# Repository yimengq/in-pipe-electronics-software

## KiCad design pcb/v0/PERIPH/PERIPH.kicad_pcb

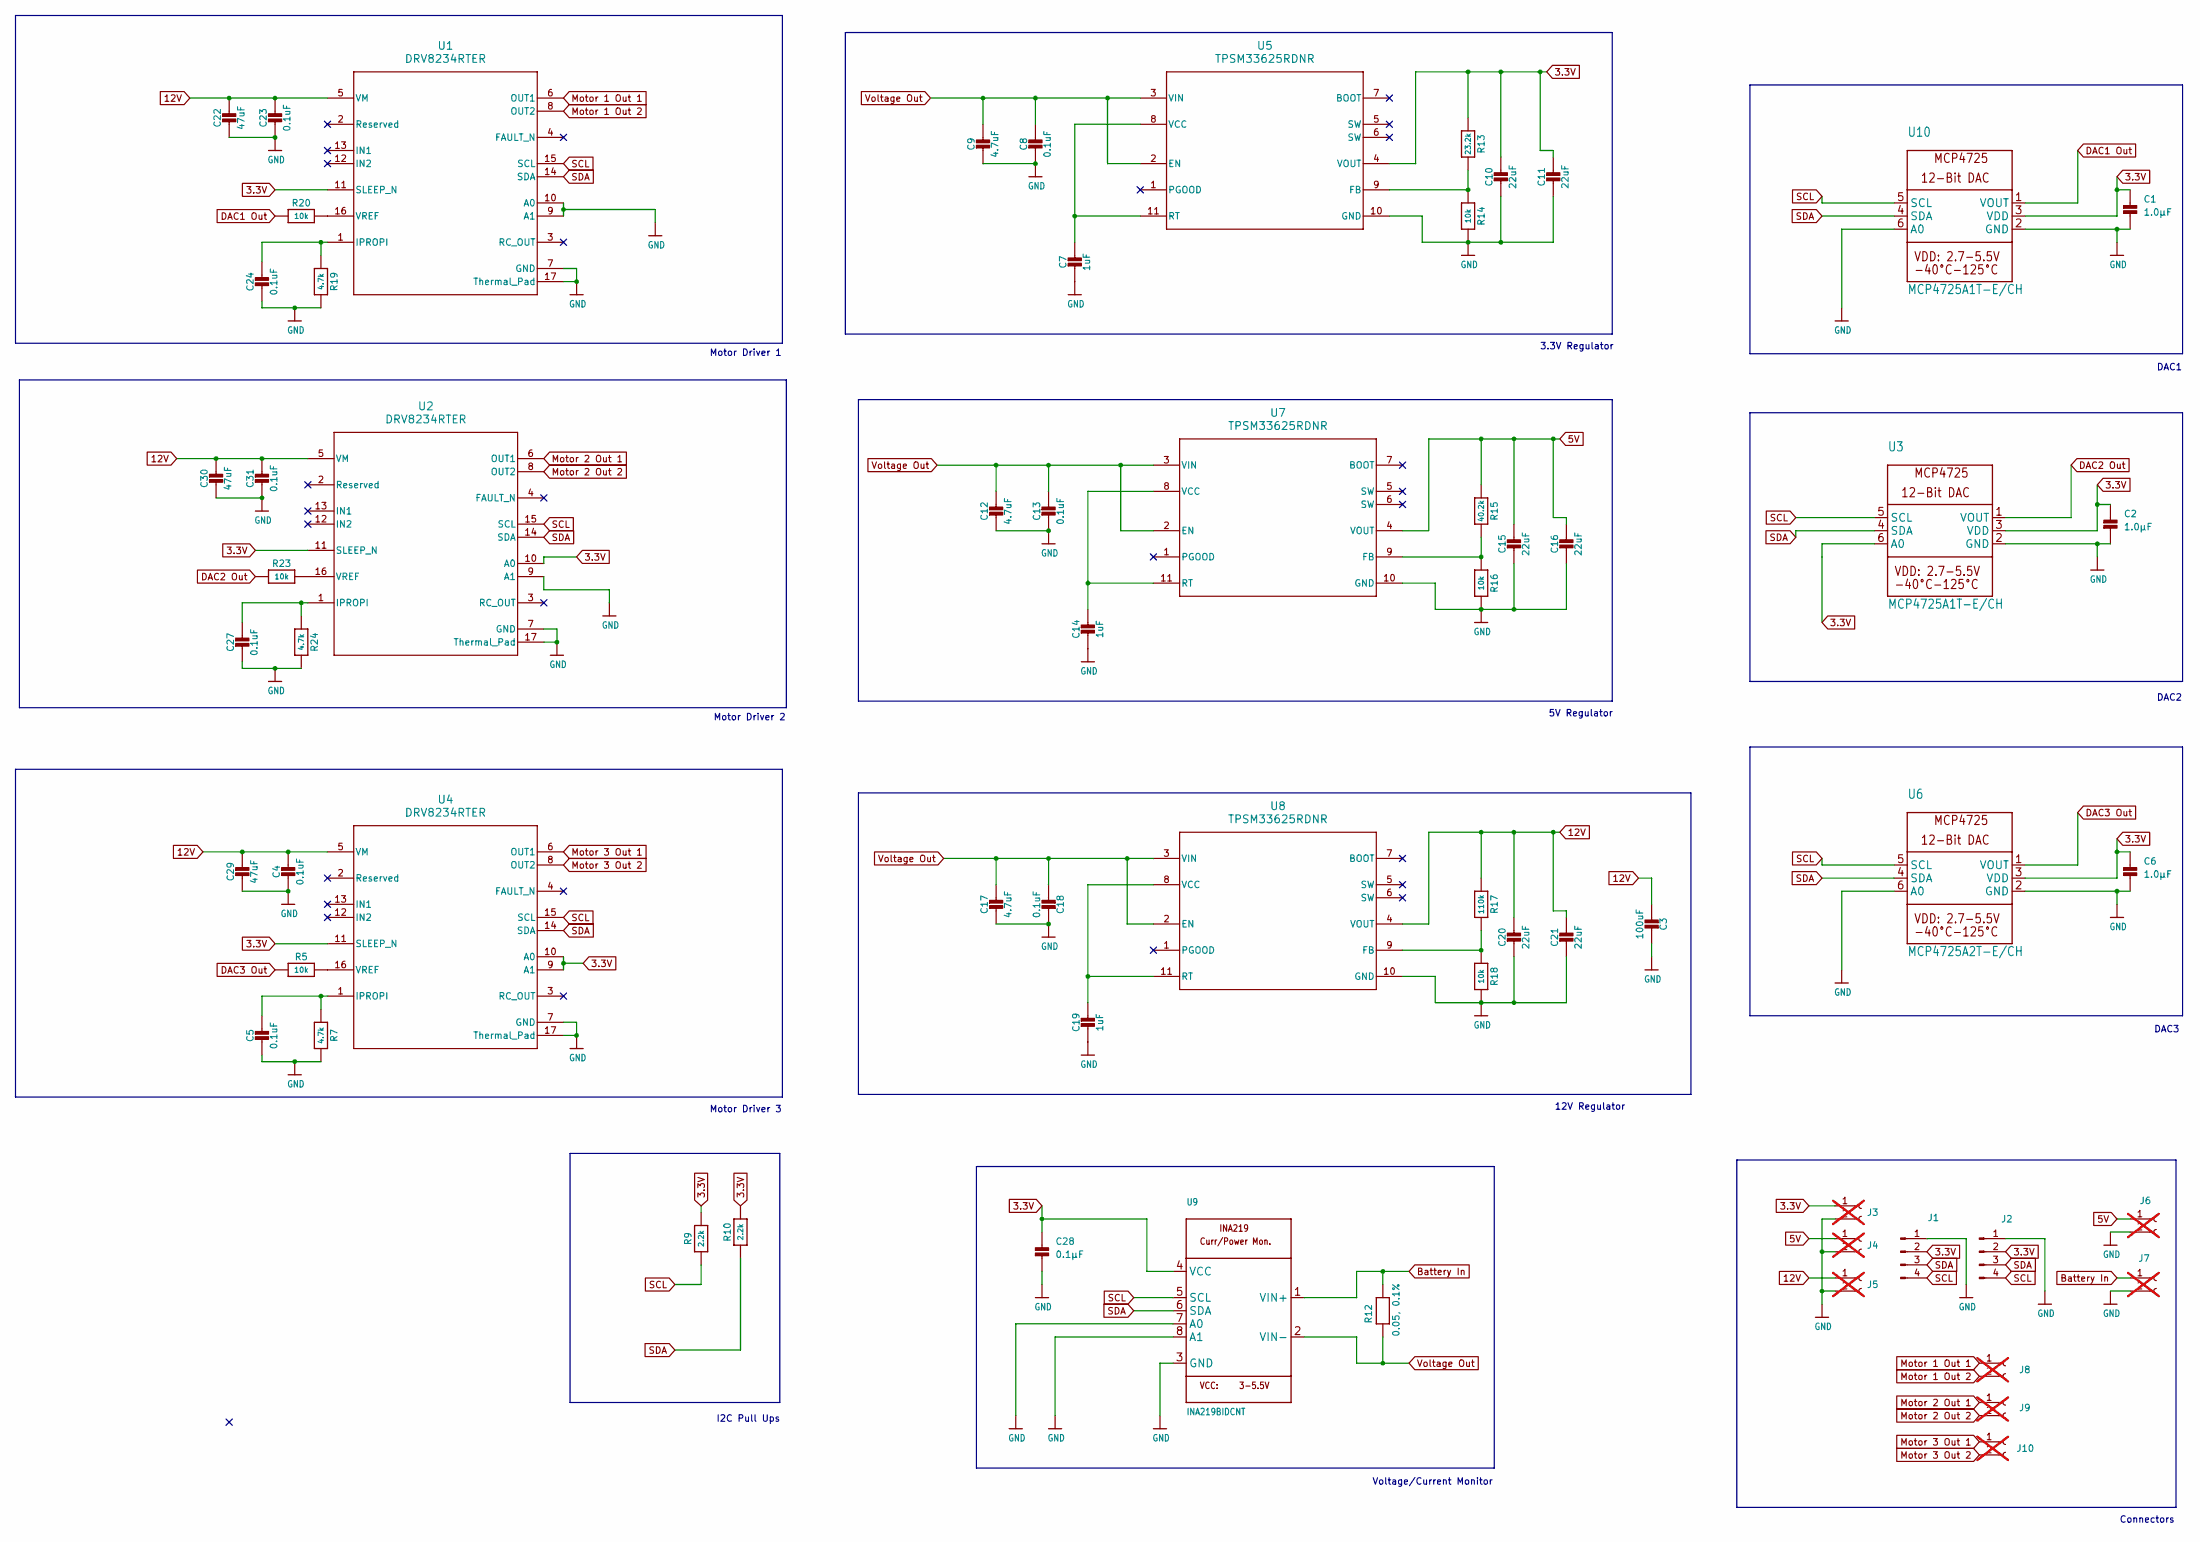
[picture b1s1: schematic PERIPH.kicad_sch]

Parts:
C1, C2, C6: 1.0µF; R_0603_1608Metric; MPN CL10B105KP8NNNC
C3: 100uF; PCAP_EEHZ_G_PAN-L; MPN EEH-ZA1H101P
C4, C5, C8, C13, C18, C23, C24, C27, C31: 0.1uF; R_0603_1608Metric; MPN C0603C104K3RACTU
C7, C14, C19: 1uF; R_0603_1608Metric; MPN CL10B105KP8NNNC
C9, C12, C17: 4.7uF; R_0805_2012Metric; MPN TMK212AB7475KG-T
C10, C11, C15, C16, C20, C21: 22uF; CAPC3225X270N; MPN CL32B226KAJNNNE
C22, C29, C30: 47uF; R_0603_1608Metric; MPN KTS250B476M76N0T00
C28: 0.1µF; R_0603_1608Metric; MPN C0603C104K3RACTU
J1, J2: JST SH 4 pin; CONN_SM04B-SRSS-TB_JST; MPN SM04B-SRSS-TB
J3, J4, J5, J6, J7, J8, J9, J10: Conn_01x02_Socket; PinSocket_1x02_P2.00mm_Vertical; not fitted
R5, R14, R16, R18, R20, R23: 10k; R_0603_1608Metric; MPN RC0603FR-0710KL
R7, R19, R24: 4.7k; R_0603_1608Metric; MPN CR0603-JW-472ELF
R9, R10: 2.2k; R_0603_1608Metric; MPN CR0603-FX-2201ELF
R12: 0.05, 0.1%; R_2512_6332Metric; MPN HoCG25122R050A4
R13: 23.2k; R_0603_1608Metric; MPN RC0603FR-0723K2L
R15: 40.2k; R_0603_1608Metric; MPN RC0603FR-0740K2L
R17: 110k; R_0603_1608Metric; MPN CRCW0603110KFKEAC
U1, U2, U4: DRV8234RTER; RTE0016C-IPC_A; MPN DRV8234RTER
U3, U10: MCP4725A1T-E/CH; SOT-23-6_MC_MCH; MPN MCP4725A1T-E/CH
U5, U7, U8: TPSM33625RDNR; RDN0011A-MFG; MPN TPSM33625RDNR
U6: MCP4725A2T-E/CH; SOT-23-6_MC_MCH; MPN MCP4725A2T-E/CH
U9: INA219BIDCNT; SOT65P280X145-8N; MPN INA219BIDCNT

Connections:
3.3V: C1.1, C2.1, C6.1, C10.1, C11.1, C28.1, J1.2, J2.2, J3.1, R9.2, R10.2, R13.1, U1.11 (SLEEP_N), U2.10 (A0), U2.11 (SLEEP_N), U3.3 (VDD), U3.6 (A0), U4.9 (A1), U4.10 (A0), U4.11 (SLEEP_N), U5.4 (VOUT), U6.3 (VDD), U9.4 (VCC), U10.3 (VDD)
5V: C15.1, C16.1, J4.1, J6.1, R15.1, U7.4 (VOUT)
12V: C3.1, C4.1, C20.1, C21.1, C22.1, C23.1, C29.1, C30.1, C31.1, J5.1, R17.1, U1.5 (VM), U2.5 (VM), U4.5 (VM), U8.4 (VOUT)
Battery In: J7.1, R12.2, U9.1 (VIN+)
DAC1 Out: R20.1, U10.1 (VOUT)
DAC2 Out: R23.1, U3.1 (VOUT)
DAC3 Out: R5.1, U6.1 (VOUT)
GND: C1.2, C2.2, C3.2, C4.2, C5.2, C6.2, C7.2, C8.2, C9.2, C10.2, C11.2, C12.2, C13.2, C14.2, C15.2, C16.2, C17.2, C18.2, C19.2, C20.2, C21.2, C22.2, C23.2, C24.2, C27.2, C28.2, C29.2, C30.2, C31.2, J1.1, J2.1, J3.2, J4.2, J5.2, J6.2, J7.2, R7.2, R14.2, R16.2, R18.2, R19.2, R24.2, U1.7 (GND), U1.9 (A1), U1.10 (A0), U1.17 (Thermal_Pad), U2.7 (GND), U2.9 (A1), U2.17 (Thermal_Pad), U3.2 (GND), U4.7 (GND), U4.17 (Thermal_Pad), U5.10 (GND), U6.2 (GND), U6.6 (A0), U7.10 (GND), U8.10 (GND), U9.3 (GND), U9.7 (A0), U9.8 (A1), U10.2 (GND), U10.6 (A0)
Motor 1 Out 1: J8.1, U1.6 (OUT1)
Motor 1 Out 2: J8.2, U1.8 (OUT2)
Motor 2 Out 1: J9.1, U2.6 (OUT1)
Motor 2 Out 2: J9.2, U2.8 (OUT2)
Motor 3 Out 1: J10.1, U4.6 (OUT1)
Motor 3 Out 2: J10.2, U4.8 (OUT2)
unnamed: C24.1, R19.1, U1.1 (IPROPI)
unnamed: R20.2, U1.16 (VREF)
unnamed: C27.1, R24.1, U2.1 (IPROPI)
unnamed: R23.2, U2.16 (VREF)
unnamed: C5.1, R7.1, U4.1 (IPROPI)
unnamed: R5.2, U4.16 (VREF)
unnamed: R13.2, R14.1, U5.9 (FB)
unnamed: C7.1, U5.8 (VCC), U5.11 (RT)
unnamed: R15.2, R16.1, U7.9 (FB)
unnamed: C14.1, U7.8 (VCC), U7.11 (RT)
unnamed: R17.2, R18.1, U8.9 (FB)
unnamed: C19.1, U8.8 (VCC), U8.11 (RT)
SCL: J1.4, J2.4, R9.1, U1.15 (SCL), U2.15 (SCL), U3.5 (SCL), U4.15 (SCL), U6.5 (SCL), U9.5 (SCL), U10.5 (SCL)
SDA: J1.3, J2.3, R10.1, U1.14 (SDA), U2.14 (SDA), U3.4 (SDA), U4.14 (SDA), U6.4 (SDA), U9.6 (SDA), U10.4 (SDA)
Voltage Out: C8.1, C9.1, C12.1, C13.1, C17.1, C18.1, R12.1, U5.2 (EN), U5.3 (VIN), U7.2 (EN), U7.3 (VIN), U8.2 (EN), U8.3 (VIN), U9.2 (VIN-)

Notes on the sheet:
Motor Driver 3
Motor Driver 2
I2C Pull Ups
DAC1
3.3V Regulator
Motor Driver 1
Voltage/Current Monitor
DAC2
Connectors
5V Regulator
12V Regulator
DAC3

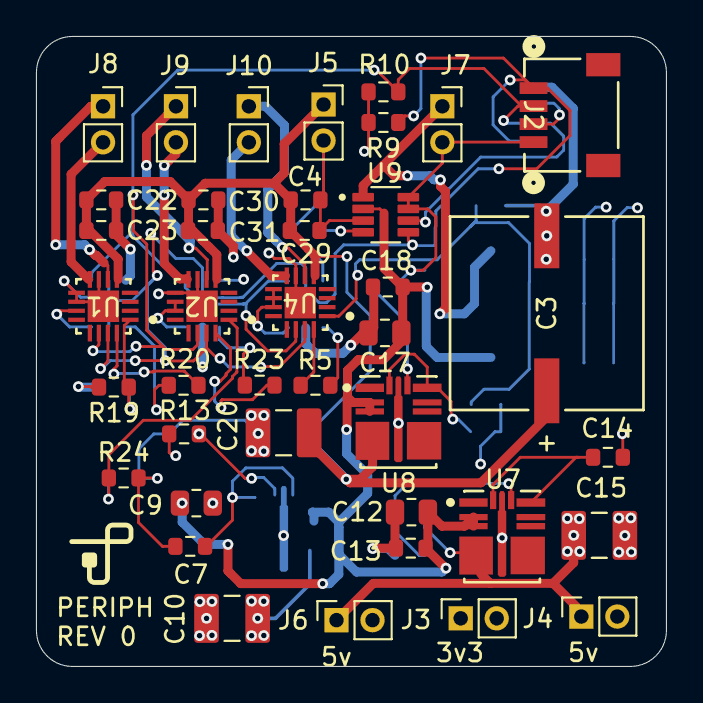
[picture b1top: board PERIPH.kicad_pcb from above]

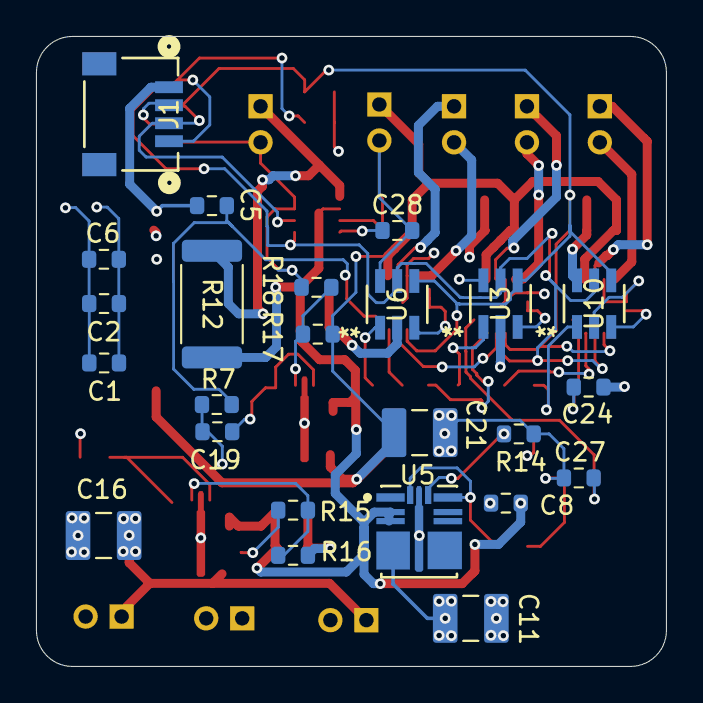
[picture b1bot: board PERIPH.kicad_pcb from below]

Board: 4 copper layers, 35.0 x 35.0 mm, 65 parts (24 on the bottom side), 29 nets.

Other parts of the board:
g: LOGO; logo

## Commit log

2025-12-21 Add gitignore for KiCad and local files
2025-12-21 reorganized
2025-12-22 Updated Libraries and Added Excel Sheet
2025-12-23 Updated with connectors and through holes
2025-12-23 Minor JST voltage Modification
2025-12-29 Fixed minor addressing issues
2025-12-29 Fixed merge issues
2025-12-29 Added Library Folder
2025-12-29 gitignore
2025-12-29 clean main
2025-12-30 PERIPH REV0 - layout and schematic
2025-12-30 finish PERIPH V0
